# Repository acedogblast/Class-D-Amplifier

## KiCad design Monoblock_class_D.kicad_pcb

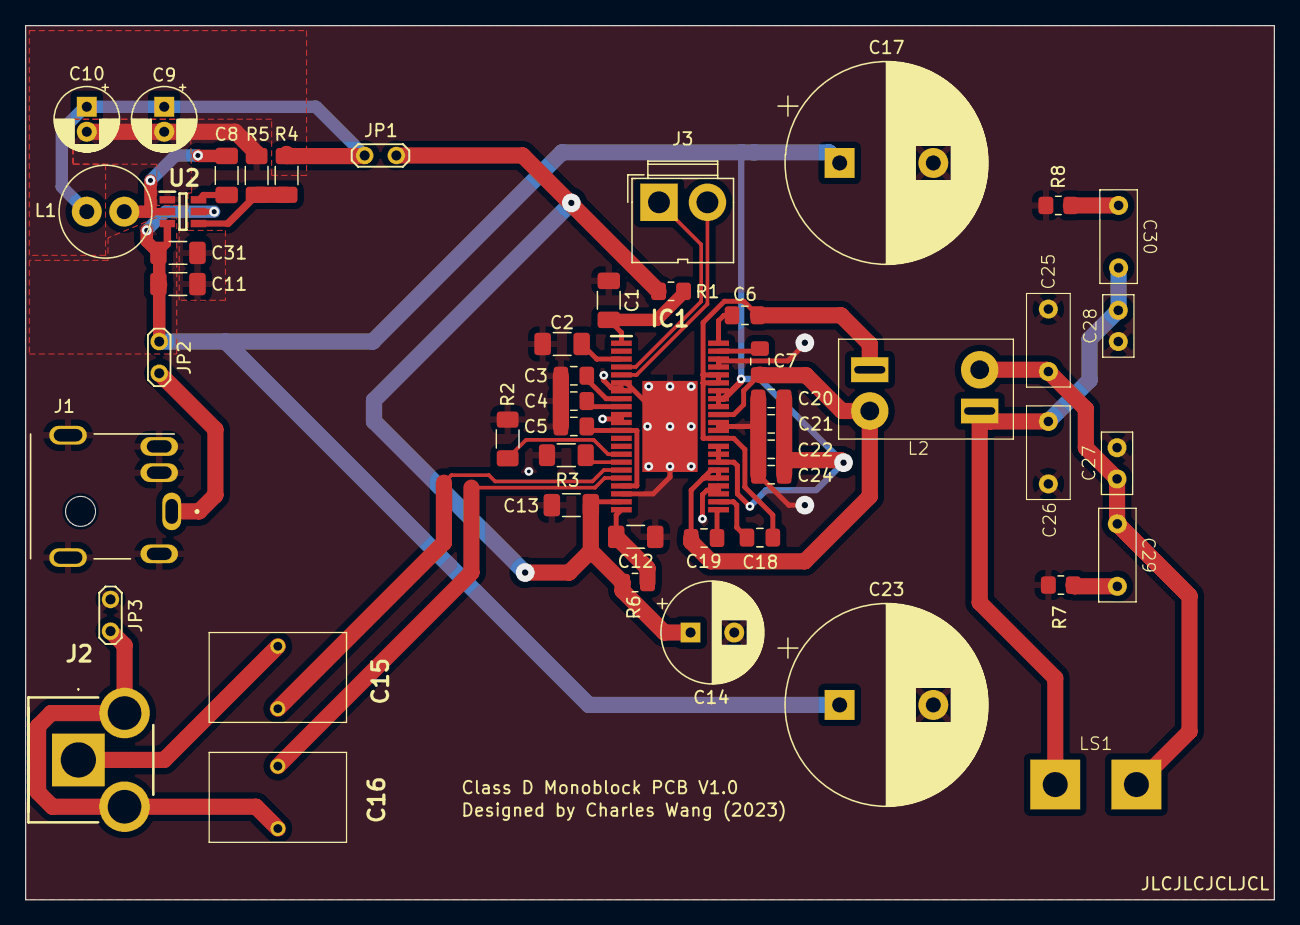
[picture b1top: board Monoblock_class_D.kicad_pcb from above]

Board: 4 copper layers, 100.0 x 70.0 mm, 50 parts (0 on the bottom side), 31 nets.

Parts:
C1, C2, C8, C12, C13, C31: 100nF; C_1206_3216Metric_Pad1.33x1.80mm_HandSolder
C3: 10nF; C_0805_2012Metric_Pad1.18x1.45mm_HandSolder
C4, C5, C20, C21, C22, C24: 1uF; C_0805_2012Metric_Pad1.18x1.45mm_HandSolder
C6, C7, C18, C19: 33nF; C_0805_2012Metric_Pad1.18x1.45mm_HandSolder
C9, C10: 10uF; CP_Radial_D5.0mm_P2.00mm
C11: 4.7uF; C_1206_3216Metric_Pad1.33x1.80mm_HandSolder
C14: 470uF 25V; CP_Radial_D8.0mm_P3.50mm
C15, C16: 10uF (film); MKS2B051001N00KSSD
C17, C23: 1000uF; CP_Radial_D16.0mm_P7.50mm
C25, C26: 680nF; MKS2B036801C00
C27, C28: 1nF; FKP0C011000B00
C29, C30: 10nF; MKP2F021001B00
IC1: TPA3244DDWR; SOP64P810X120-45M
J1: PJ-076A; CUI_PJ-076A
J2: PJRAN1X1U01AUX
J3: status_output; JWT_A3963_1x02_P3.96mm_Vertical
JP1: 12V Jumper; TestPoint_2Pads_Pitch2.54mm_Drill0.8mm
JP2: 24V Jumper; TestPoint_2Pads_Pitch2.54mm_Drill0.8mm
JP3: Audio GND; TestPoint_2Pads_Pitch2.54mm_Drill0.8mm
L1: 8.2uH; L_Radial_D7.0mm_P3.0mm
L2: 22uHx2; Dual_Inductor_Wurth_744011480220
LS1: Speaker; SpeakerOutWire
R1, R6, R7, R8: 3R3; R_0805_2012Metric_Pad1.20x1.40mm_HandSolder
R2: 30K (1%); R_1206_3216Metric_Pad1.30x1.75mm_HandSolder
R3: 30k; R_1206_3216Metric_Pad1.30x1.75mm_HandSolder
R4: 100K (1%); R_1206_3216Metric_Pad1.30x1.75mm_HandSolder
R5: 5.23K (1%); R_1206_3216Metric_Pad1.30x1.75mm_HandSolder
U2: LMR51420YDDCR; SOT95P280X110-6N

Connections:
+12V: C9.1, C10.1, C13.2, C14.1, IC1.21 (VDD), JP1.1 (A), JP1.2 (B), L1.1, R1.1, R4.2, R6.2
+24V: C11.2, C17.1, C20.2, C21.1, C22.2, C23.1, C24.1, C31.1, IC1.29 (PVDD_AB_1), IC1.30 (PVDD_AB_2), IC1.31 (PVDD_AB_3), IC1.36 (PVDD_CD_1), IC1.37 (PVDD_CD_2), IC1.38 (PVDD_CD_3), JP2.1 (A), U2.3 (VIN), U2.5 (EN)
GND: C1.1, C2.1, C3.1, C4.1, C5.1, C9.2, C10.2, C11.1, C12.2, C13.1, C14.2, C17.2, C20.1, C21.2, C22.1, C23.2, C24.2, C25.2, C26.1, C27.2, C28.1, C31.2, IC1.6 (INPUT_D), IC1.7 (INPUT_C), IC1.10 (GND_1), IC1.11 (GND_2), IC1.20 (M1), IC1.25 (GND_3), IC1.26 (GND_4), IC1.33 (GND_5), IC1.34 (GND_6), IC1.41 (GND_7), IC1.42 (GND_8), IC1.45 (EP), J1.2, J1.3, J1.4, J1.5 (SHIELD), J1.6 (SHIELD), JP3.1 (A), R2.1, R3.1, R5.1, R7.2, R8.1, U2.1 (GND)
unnamed: C25.1, C27.1, C29.1, L2.2, LS1.1
unnamed: C26.2, C28.2, C30.2, L2.3, LS1.2
unnamed: C29.2, R7.1
unnamed: C30.1, R8.2
unnamed: C4.2, IC1.9 (AVDD)
unnamed: C19.1, IC1.23 (BST_A)
unnamed: C18.1, IC1.24 (BST_B)
unnamed: C7.1, IC1.43 (BST_C)
unnamed: C6.1, IC1.44 (BST_D)
unnamed: C3.2, IC1.8 (C_START)
unnamed: C5.2, IC1.12 (DVDD), IC1.19 (M2)
unnamed: IC1.15 (FREQ_ADJ), R2.2
unnamed: C12.1, IC1.22 (GVDD_AB), R6.1
unnamed: C1.2, IC1.1 (GVDD_CD), R1.2
unnamed: C16.2, IC1.18 (INPUT_A)
unnamed: C15.2, IC1.17 (INPUT_B)
unnamed: IC1.16 (OC_ADJ), R3.2
unnamed: C7.2, C19.2, IC1.27 (OUT_A_1), IC1.28 (OUT_A_2), IC1.35 (OUT_C), L2.4
unnamed: C6.2, C18.2, IC1.32 (OUT_B), IC1.39 (OUT_D_1), IC1.40 (OUT_D_2), L2.1
unnamed: C2.2, IC1.3 (VBG)
unnamed: IC1.4 (~FAULT), J3.1
unnamed: IC1.5 (~RESET), J3.2
unnamed: C16.1, J2.2 (TIP), J2.3 (SHUNT), JP3.2 (B)
unnamed: C15.1, J2.1 (SLEEVE)
unnamed: J1.1, JP2.2 (B)
unnamed: C8.1, U2.6 (CB)
unnamed: R4.1, R5.2, U2.4 (FB)
unnamed: C8.2, L1.2, U2.2 (SW)
